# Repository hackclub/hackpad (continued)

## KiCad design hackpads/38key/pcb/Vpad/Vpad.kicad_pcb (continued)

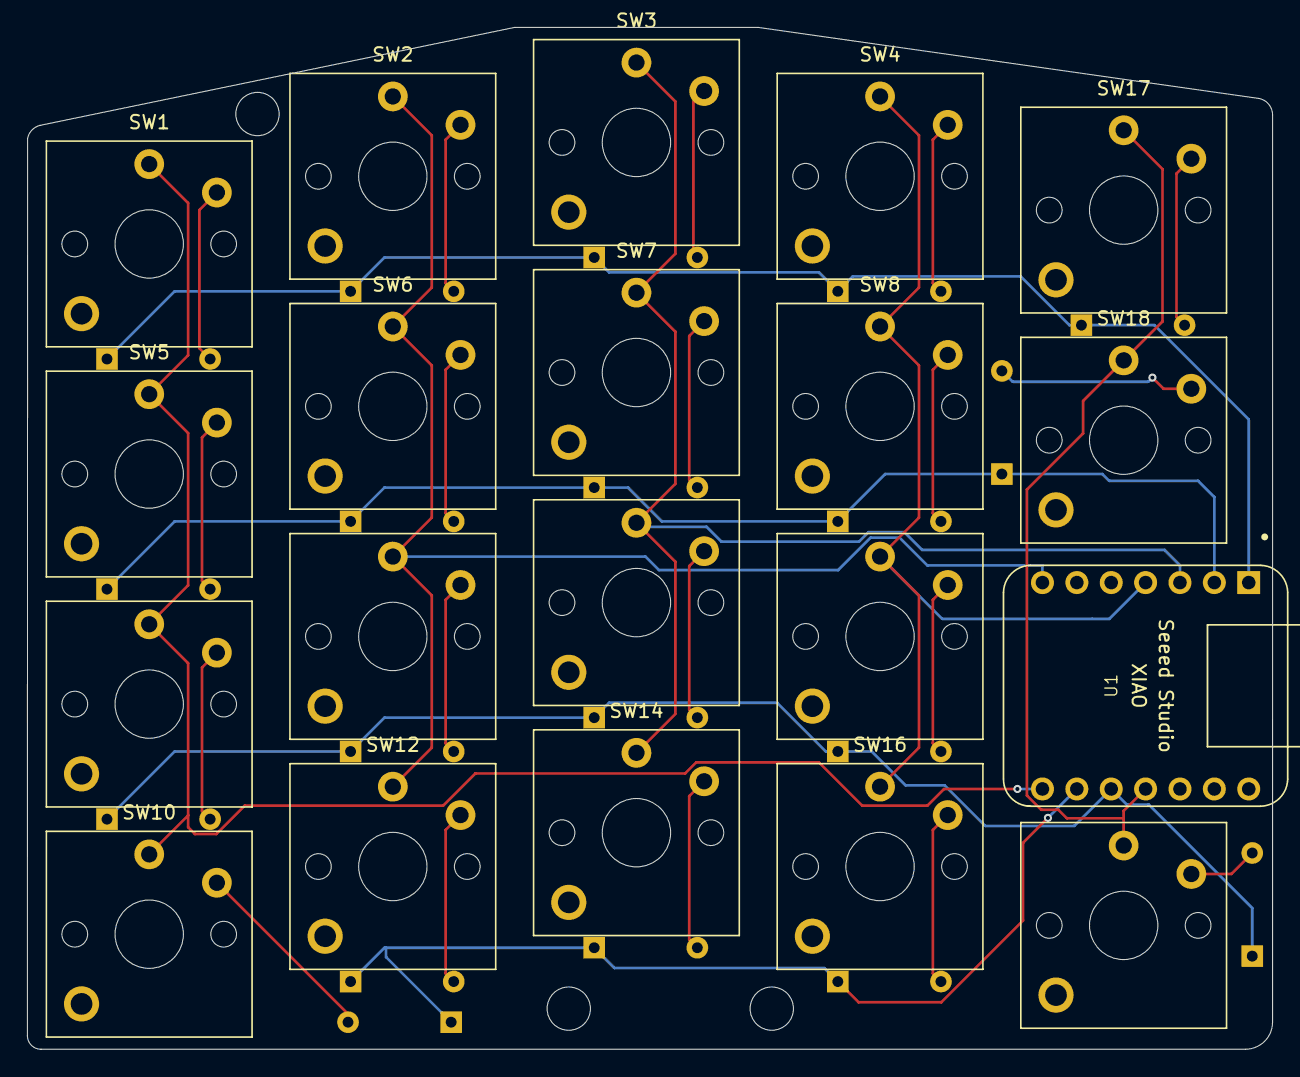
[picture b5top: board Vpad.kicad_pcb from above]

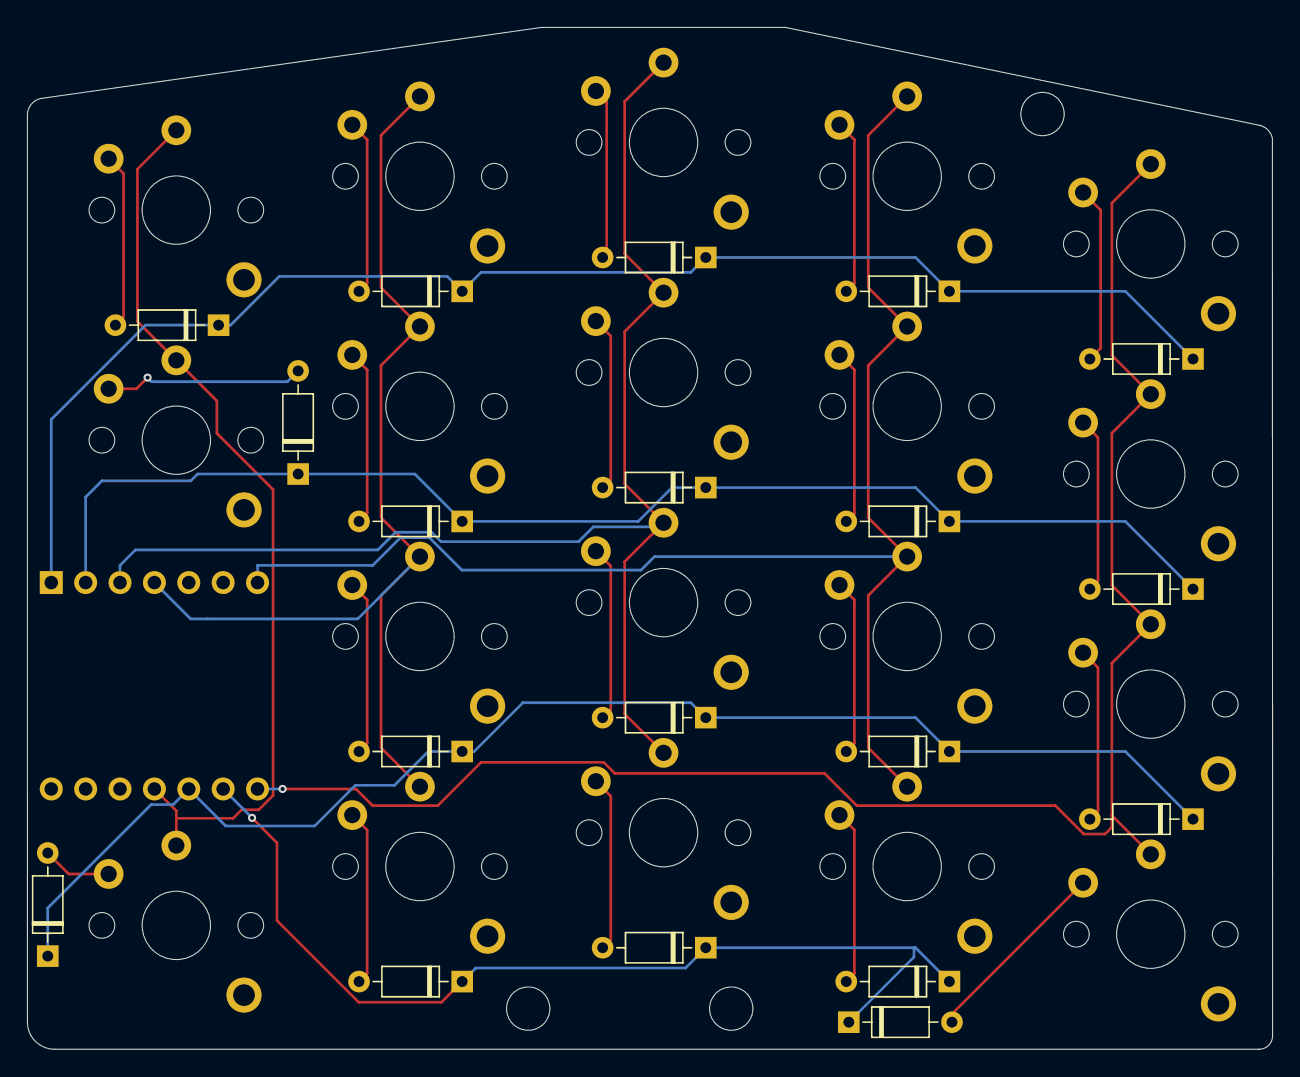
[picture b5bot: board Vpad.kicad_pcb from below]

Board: 2 copper layers, 92.0 x 75.5 mm, 39 parts (19 on the bottom side), 28 nets.

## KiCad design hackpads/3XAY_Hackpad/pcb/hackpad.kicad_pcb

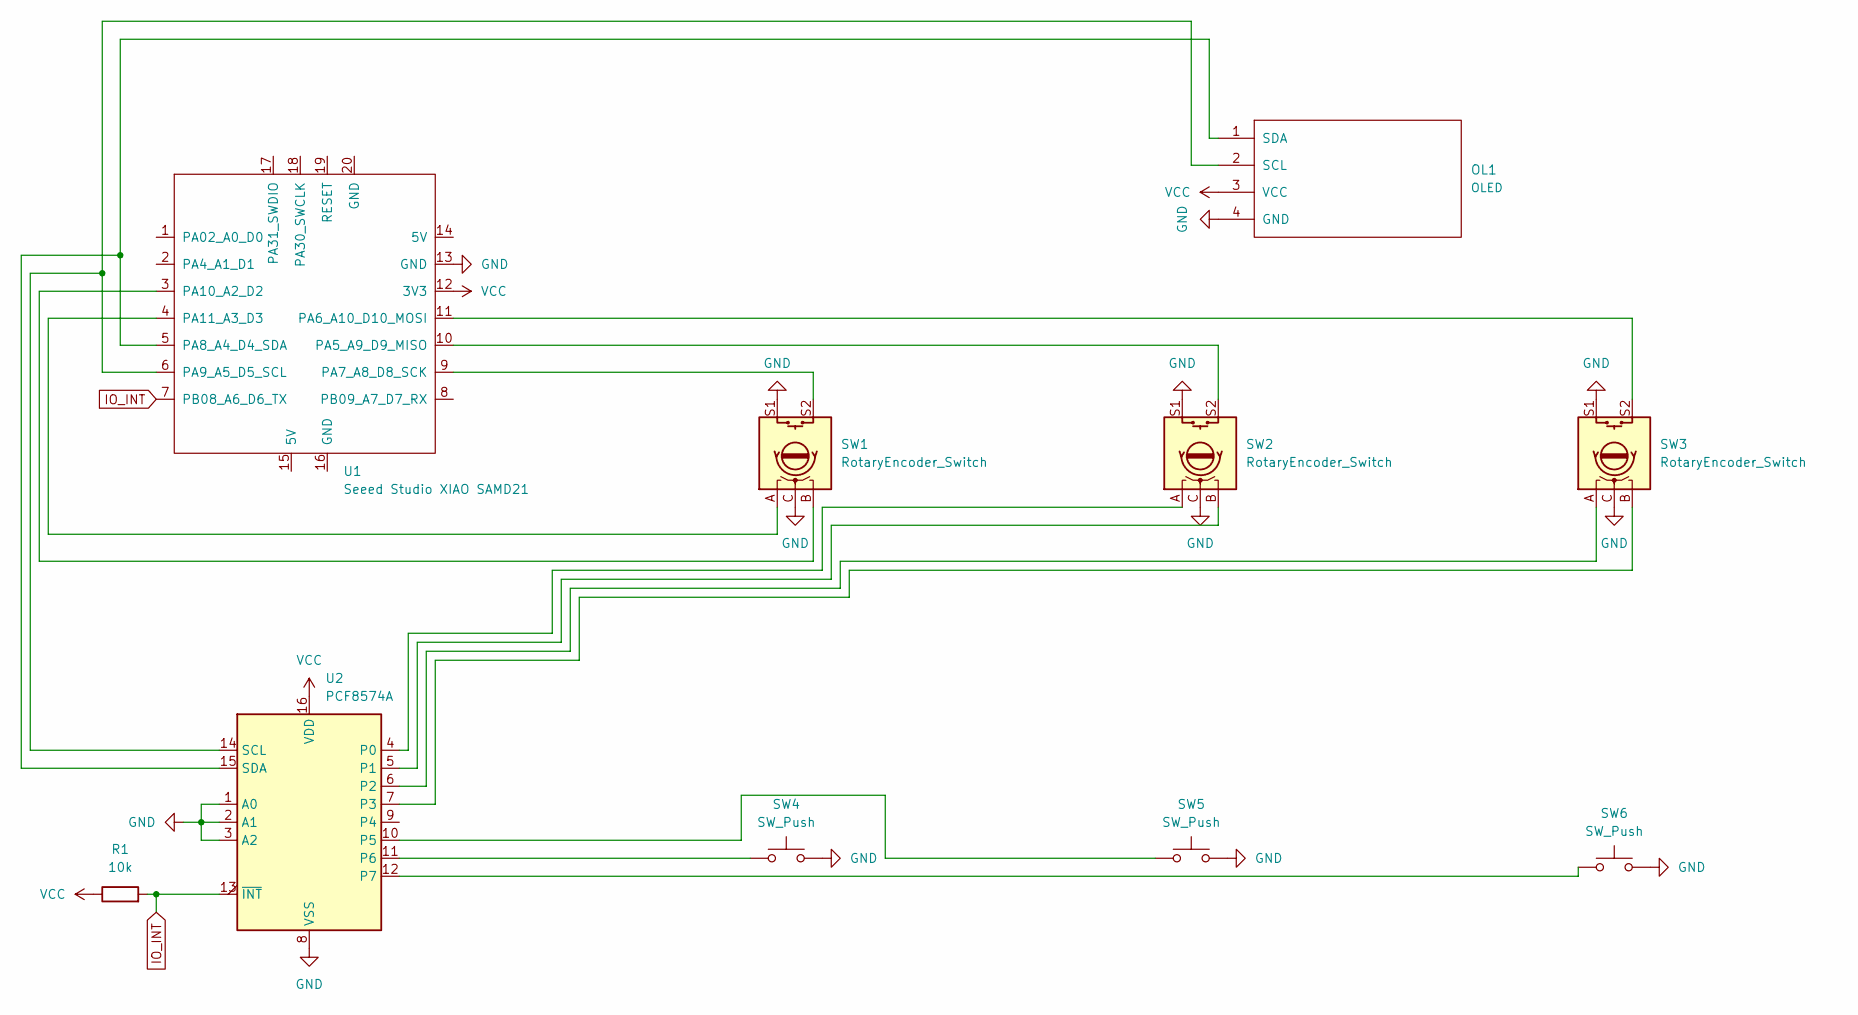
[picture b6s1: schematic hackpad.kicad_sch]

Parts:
OL1: OLED; SSD1306-0.91-OLED-4pin-128x32
R1: 10k; R_Axial_DIN0207_L6.3mm_D2.5mm_P10.16mm_Horizontal
SW1, SW2, SW3: RotaryEncoder_Switch; RotaryEncoder_Alps_EC11E-Switch_Vertical_H20mm
SW4, SW5, SW6: SW_Push; SW_Cherry_MX_1.00u_PCB
U1: Seeed Studio XIAO SAMD21; XIAO-Generic-Thruhole-14P-2.54-21X17.8MM
U2: PCF8574A; DIP-16_W7.62mm

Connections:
GND: OL1.4 (GND), SW1.C, SW1.S1, SW2.C, SW2.S1, SW3.C, SW3.S1, SW4.2, SW5.2, SW6.2, U1.13 (GND), U2.1 (A0), U2.2 (A1), U2.3 (A2), U2.8 (VSS)
IO_INT: R1.2, U1.7 (PB08_A6_D6_TX), U2.13 (~INT)
unnamed: OL1.2 (SCL), U1.6 (PA9_A5_D5_SCL), U2.14 (SCL)
unnamed: OL1.1 (SDA), U1.5 (PA8_A4_D4_SDA), U2.15 (SDA)
unnamed: SW2.S2, U1.10 (PA5_A9_D9_MISO)
unnamed: SW3.S2, U1.11 (PA6_A10_D10_MOSI)
unnamed: SW1.S2, U1.9 (PA7_A8_D8_SCK)
unnamed: SW1.B, U1.3 (PA10_A2_D2)
unnamed: SW1.A, U1.4 (PA11_A3_D3)
unnamed: SW2.A, U2.4 (P0)
unnamed: SW2.B, U2.5 (P1)
unnamed: SW3.A, U2.6 (P2)
unnamed: SW3.B, U2.7 (P3)
unnamed: SW5.1, U2.10 (P5)
unnamed: SW4.1, U2.11 (P6)
unnamed: SW6.1, U2.12 (P7)
VCC: OL1.3 (VCC), R1.1, U1.12 (3V3), U2.16 (VDD)

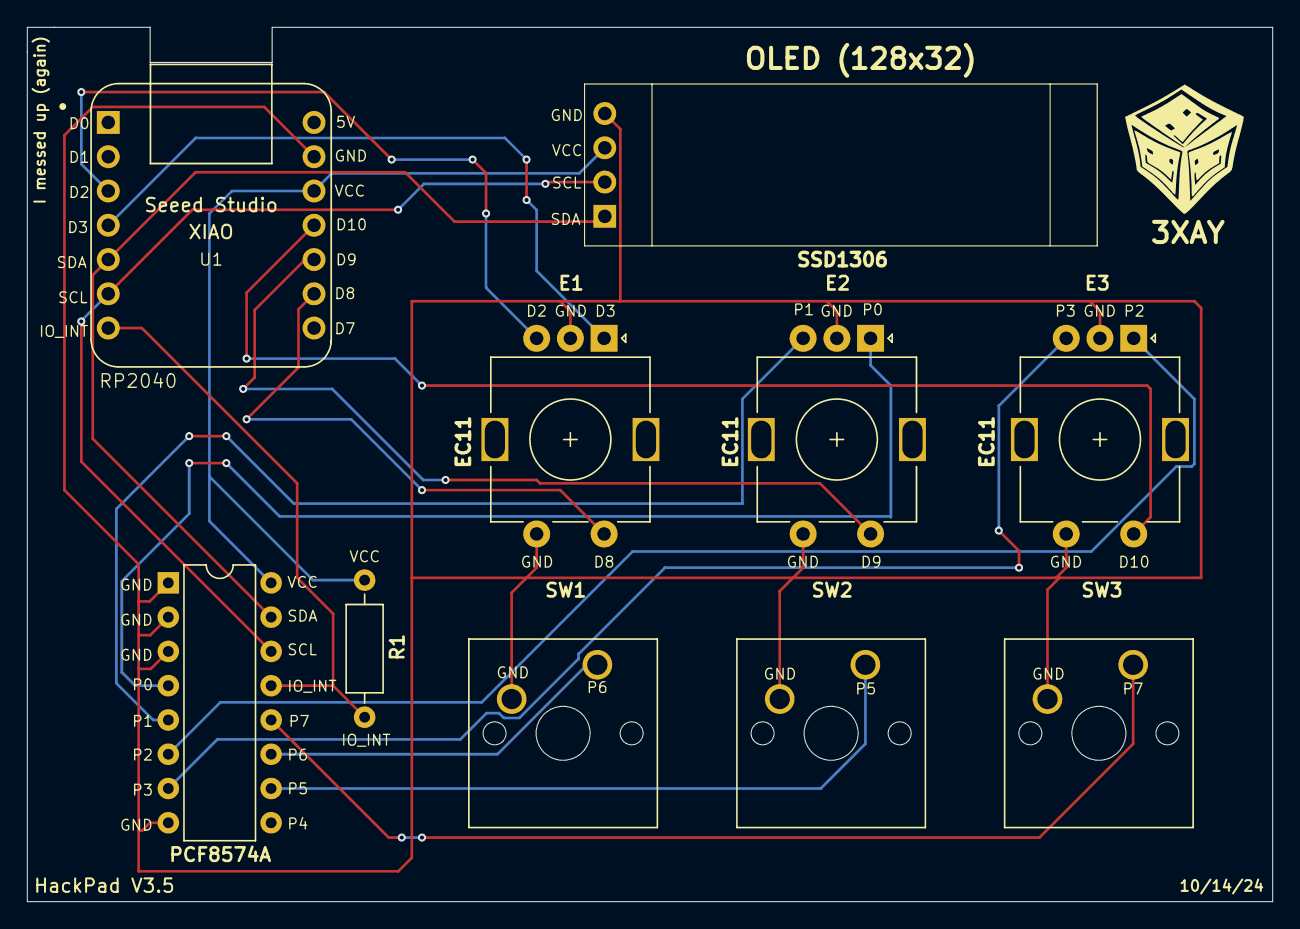
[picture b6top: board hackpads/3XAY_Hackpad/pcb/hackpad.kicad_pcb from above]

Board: 2 copper layers, 92.3 x 64.8 mm, 10 parts (0 on the bottom side), 17 nets.

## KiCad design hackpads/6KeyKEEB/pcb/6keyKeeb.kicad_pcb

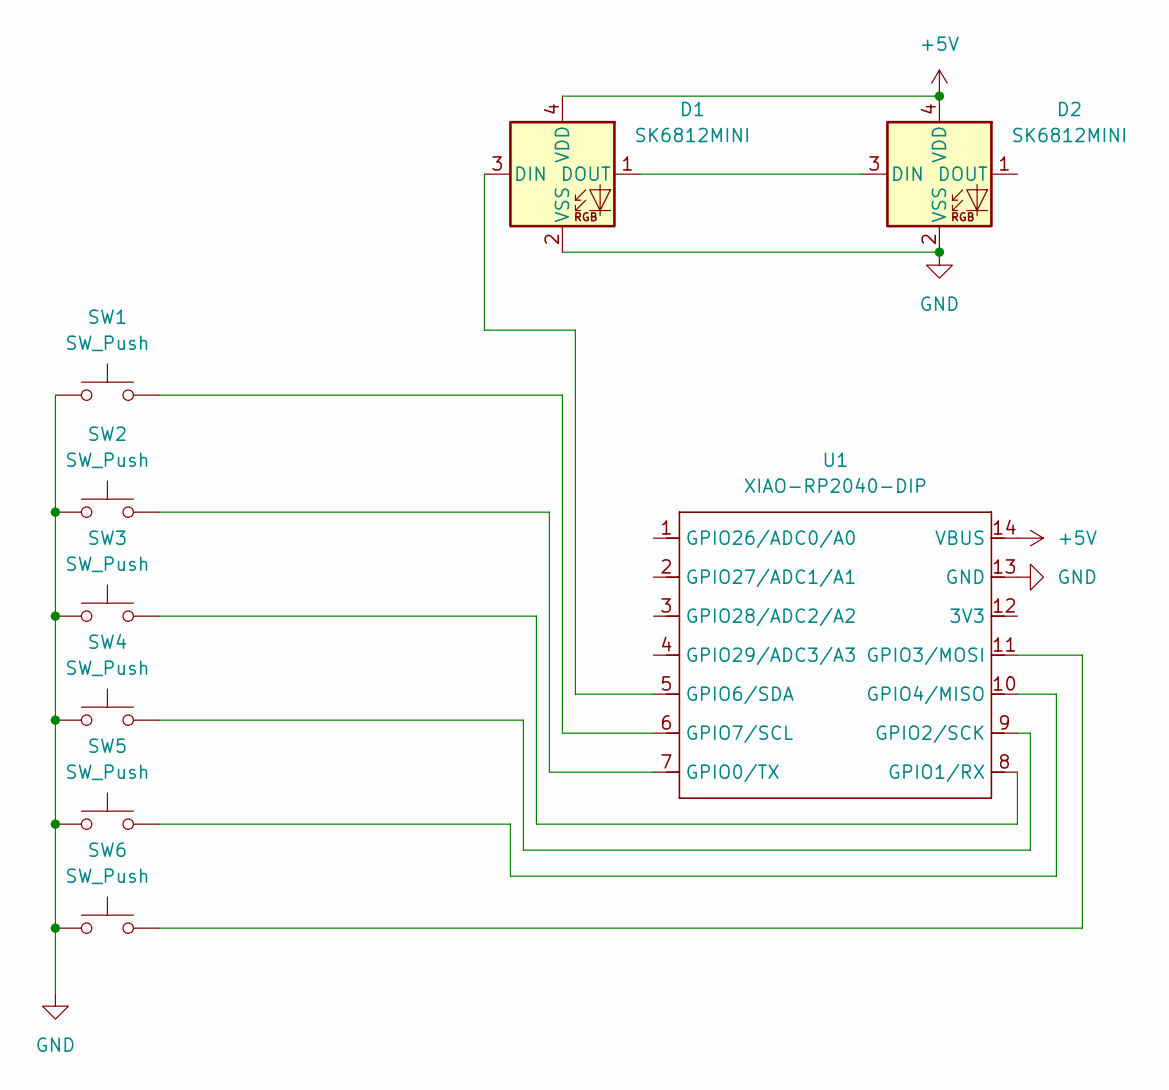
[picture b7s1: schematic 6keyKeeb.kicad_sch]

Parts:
D1, D2: SK6812MINI; LED_SK6812MINI_PLCC4_3.5x3.5mm_P1.75mm
SW1, SW2, SW3, SW4, SW5, SW6: SW_Push; SW_Cherry_MX_1.00u_PCB
U1: XIAO-RP2040-DIP

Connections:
+5V: D1.4 (VDD), D2.4 (VDD), U1.14 (VBUS)
GND: D1.2 (VSS), D2.2 (VSS), SW1.1, SW2.1, SW3.1, SW4.1, SW5.1, SW6.1, U1.13 (GND)
unnamed: D1.3 (DIN), U1.5 (GPIO6/SDA)
unnamed: D1.1 (DOUT), D2.3 (DIN)
unnamed: SW2.2, U1.7 (GPIO0/TX)
unnamed: SW3.2, U1.8 (GPIO1/RX)
unnamed: SW4.2, U1.9 (GPIO2/SCK)
unnamed: SW6.2, U1.11 (GPIO3/MOSI)
unnamed: SW5.2, U1.10 (GPIO4/MISO)
unnamed: SW1.2, U1.6 (GPIO7/SCL)

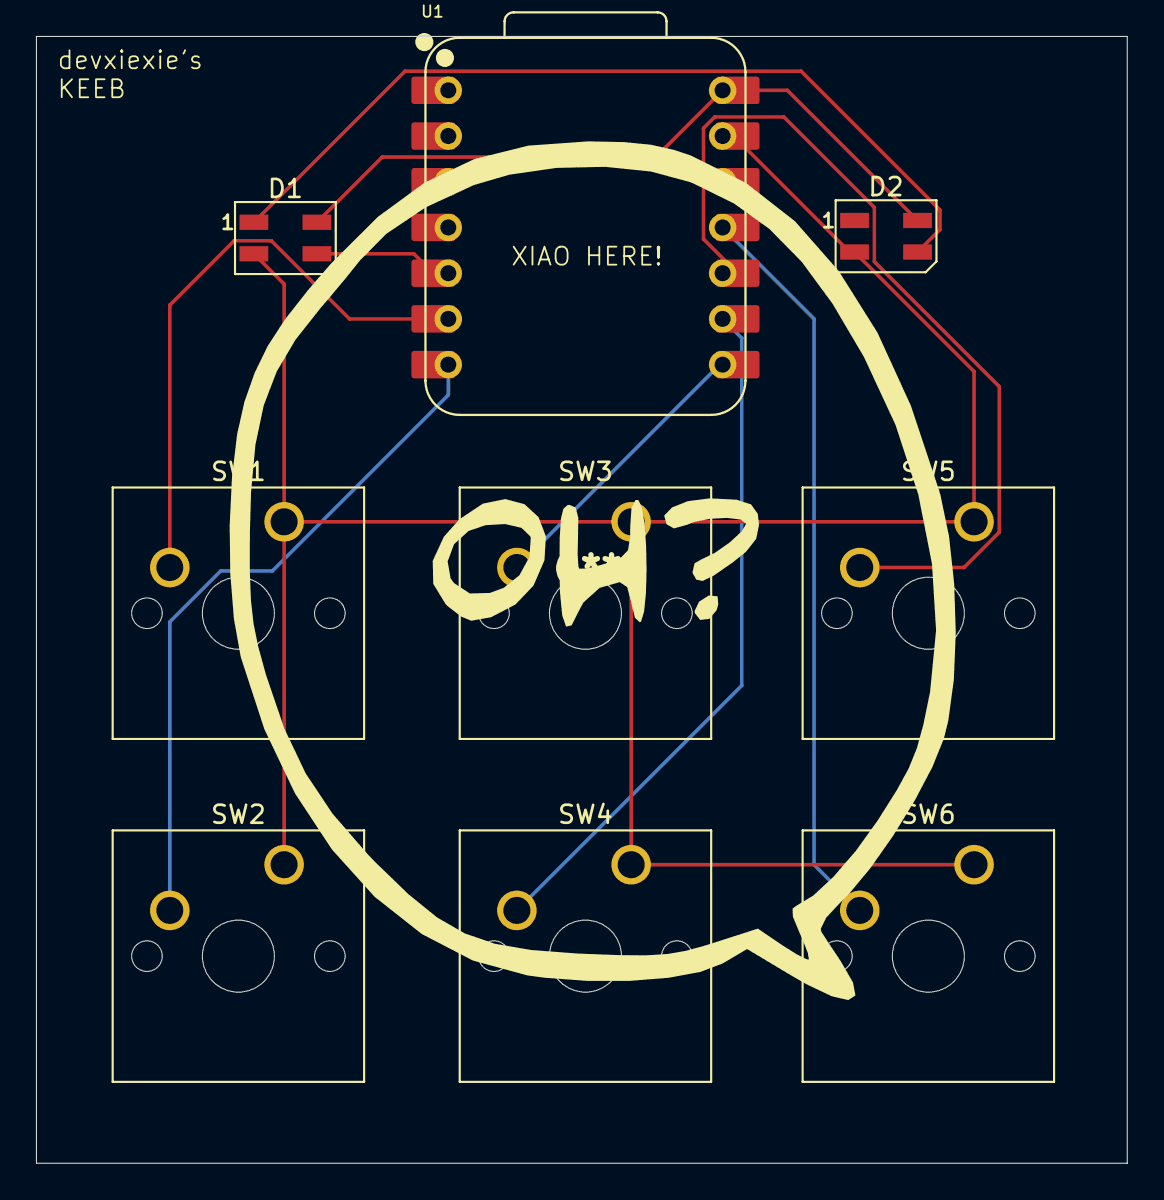
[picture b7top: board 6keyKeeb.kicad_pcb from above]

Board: 2 copper layers, 60.6 x 62.6 mm, 9 parts (0 on the bottom side), 10 nets.

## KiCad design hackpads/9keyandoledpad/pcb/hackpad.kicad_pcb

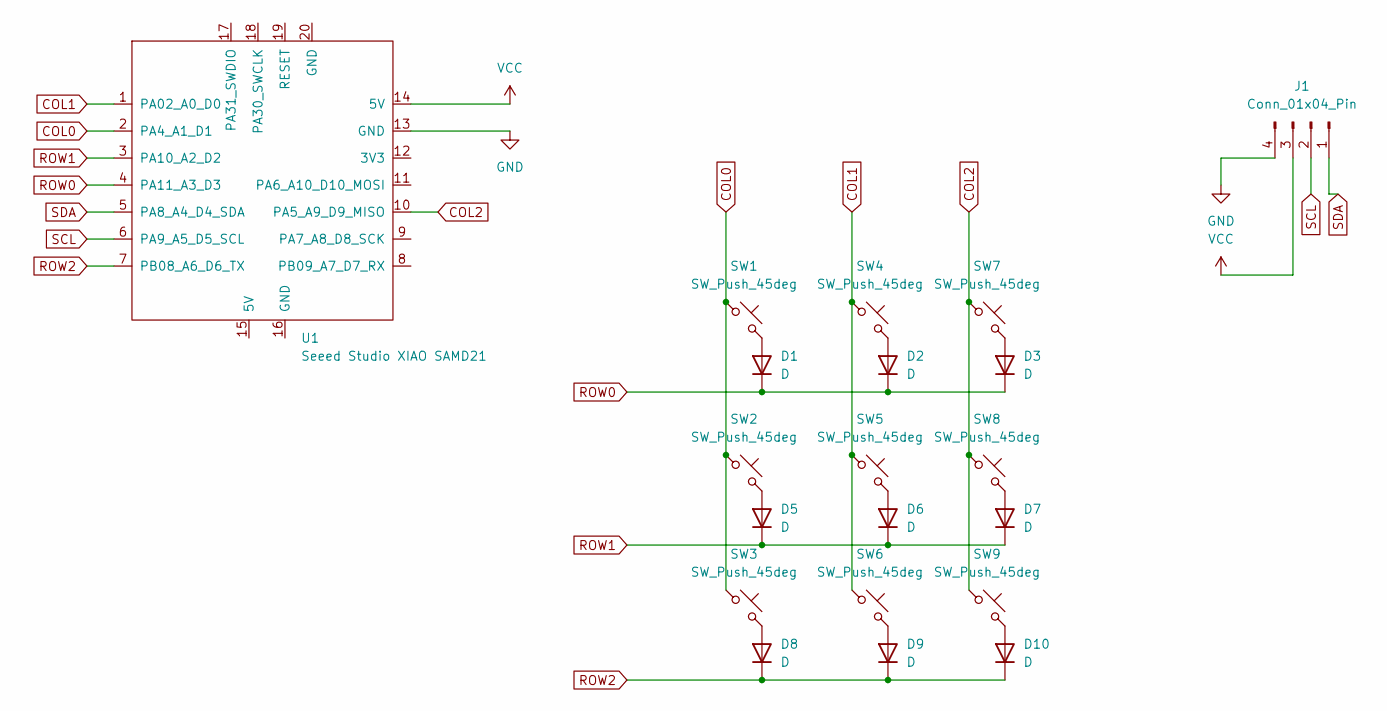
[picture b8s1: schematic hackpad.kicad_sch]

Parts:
D1, D2, D3, D5, D6, D7, D8, D9, D10: D; D_DO-35_SOD27_P7.62mm_Horizontal
J1: Conn_01x04_Pin; PinHeader_1x04_P2.54mm_Vertical
SW1, SW2, SW3, SW4, SW5, SW6, SW7, SW8, SW9: SW_Push_45deg; SW_Cherry_MX_1.00u_PCB
U1: Seeed Studio XIAO SAMD21; XIAO-SAMD21-RP2040

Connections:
COL0: SW1.1, SW2.1, SW3.1, U1.2 (PA4_A1_D1)
COL1: SW4.1, SW5.1, SW6.1, U1.1 (PA02_A0_D0)
COL2: SW7.1, SW8.1, SW9.1, U1.10 (PA5_A9_D9_MISO)
GND: J1.4, U1.13 (GND)
unnamed: D1.2 (A), SW1.2
unnamed: D2.2 (A), SW4.2
unnamed: D3.2 (A), SW7.2
unnamed: D5.2 (A), SW2.2
unnamed: D6.2 (A), SW5.2
unnamed: D7.2 (A), SW8.2
unnamed: D8.2 (A), SW3.2
unnamed: D9.2 (A), SW6.2
unnamed: D10.2 (A), SW9.2
ROW0: D1.1 (K), D2.1 (K), D3.1 (K), U1.4 (PA11_A3_D3)
ROW1: D5.1 (K), D6.1 (K), D7.1 (K), U1.3 (PA10_A2_D2)
ROW2: D8.1 (K), D9.1 (K), D10.1 (K), U1.7 (PB08_A6_D6_TX)
SCL: J1.2, U1.6 (PA9_A5_D5_SCL)
SDA: J1.1, U1.5 (PA8_A4_D4_SDA)
VCC: J1.3, U1.14 (5V)

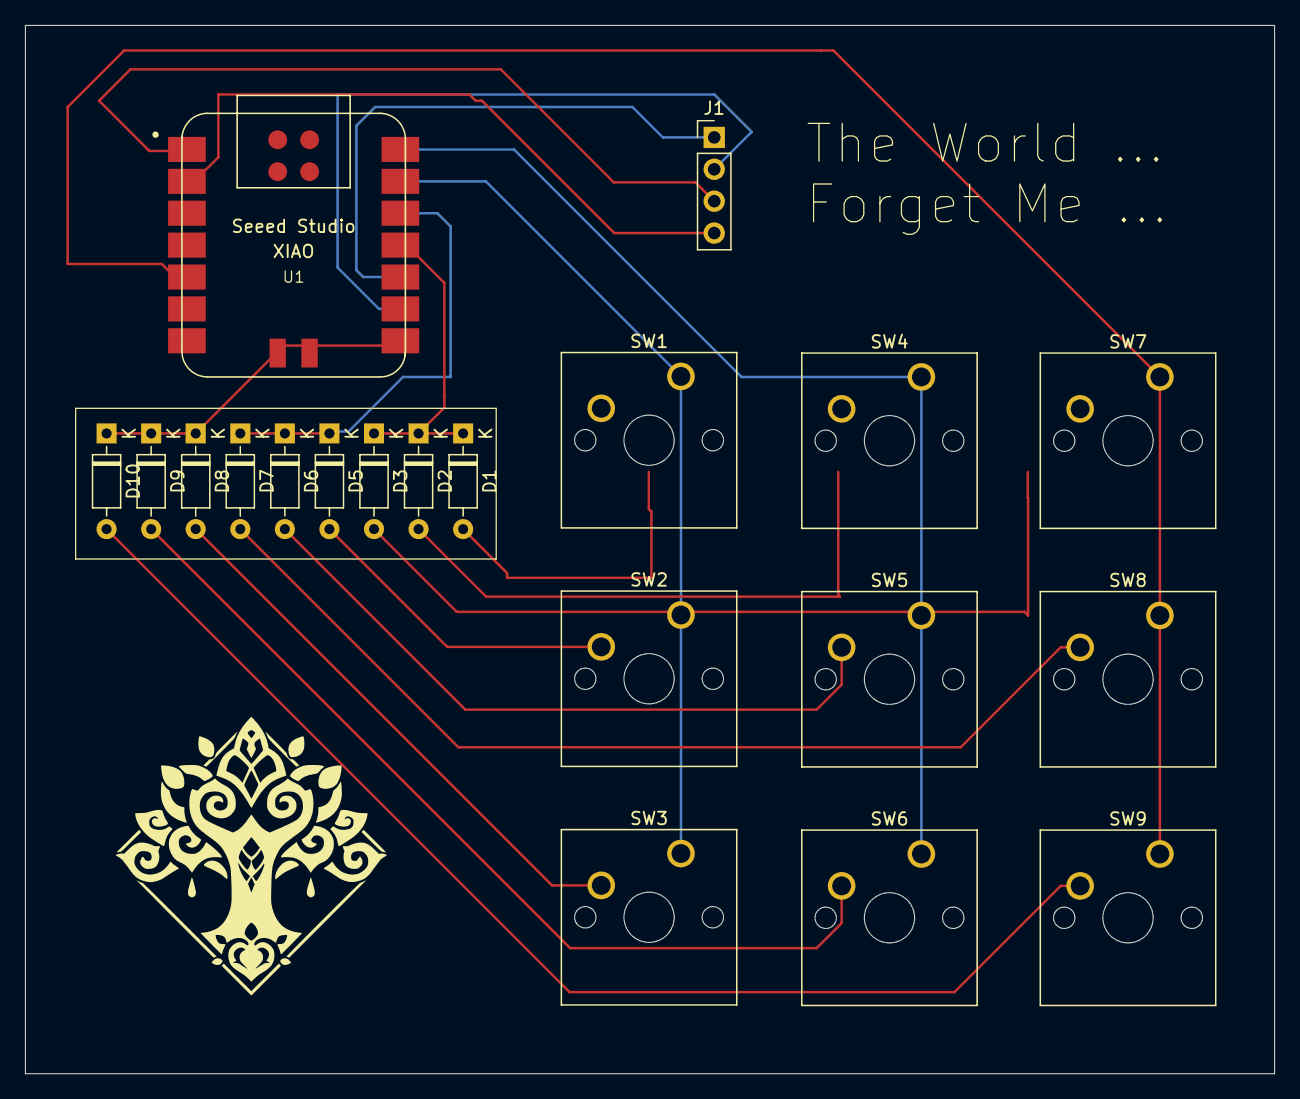
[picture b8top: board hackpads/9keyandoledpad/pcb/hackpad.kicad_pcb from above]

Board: 2 copper layers, 99.5 x 83.5 mm, 21 parts (0 on the bottom side), 19 nets.

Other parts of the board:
Logo: LOGO
